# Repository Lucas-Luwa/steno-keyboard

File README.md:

# Stenography keyboard

A custom 30-key stenography keyboard with a Waveshare RP2040-Plus 16 MB controller, Kailh Choc V1 switches, eight RGB LEDs, and a 3D-printed case with a removable travel cap.

**[V3](V3/) is the latest version.** Earlier electronics designs and case exports are in [archive/](archive/README.md).

## Start here

| What you need | Open |
|---|---|
| Assembly instructions | [Build guide](V3/build-guide.md) |
| Schematic, PCB and parts | [Electronics](V3/hardware/README.md) · [KiCad project](V3/hardware/StenoV3.kicad_pro) · [BOM](V3/hardware/bom.csv) |
| Editable CAD, STL models and printer jobs | [Mechanical guide](V3/mechanical/README.md) |
| Gerbers and drill files | [Fabrication guide](V3/manufacturing/README.md) · [Fabrication ZIP](V3/manufacturing/StenoV3-Gerbers.zip) |
| Javelin configuration and LED diagnostics | [Firmware guide](V3/firmware/README.md) |
| LED diagnostics and test results | [LED test guide](V3/firmware/led-tests/README.md) · [Results](V3/firmware/led-tests/results.md) |
| Switch-library credits and licenses | [Reference assets](third_party/README.md) |

## Onboard lighting

The keyboard uses [Javelin firmware with Lapwing dictionaries](V3/firmware/javelin/README.md) for onboard stenography. The lighting runs on the controller, with selectable idle patterns, brightness controls and a green typing indicator.

https://github.com/user-attachments/assets/ecf25d7d-600b-45e7-80ae-683e2c61e2ce

Onboard lighting patterns and controls.

## Design files

The [mechanical guide](V3/mechanical/README.md) covers the base, travel cap, insert coupon, LED jig references and keyboard assemblies.

For printing, start with [`case-bottom.stl`](V3/mechanical/stl/case-bottom.stl), [`travel-cap.stl`](V3/mechanical/stl/travel-cap.stl) and [`insert-test-coupon.stl`](V3/mechanical/stl/insert-test-coupon.stl). The [SV06/OrcaSlicer profile](V3/mechanical/README.md#sv06-slicing-settings) covers PLA settings and diagonal bed placement. Slice the current travel cap from its STL. Bambu-specific base and insert-coupon printer jobs for A1, P1S and P2S are grouped under [`print-jobs/`](V3/mechanical/print-jobs/).

The [electronics guide](V3/hardware/README.md) explains component packages, the five-row/six-column matrix and the RGB chain. GPIO assignments, switch/diode positions and LED order are also available as CSV tables alongside the KiCad project.

## Repository layout

```text
steno/
├── README.md
├── V3/
│   ├── build-guide.md
│   ├── hardware/        # KiCad project, BOM, pinout and matrix
│   ├── mechanical/
│   │   ├── solidworks/ # Editable parts and assemblies
│   │   ├── step/       # Neutral CAD references
│   │   ├── stl/        # Case, coupon and LED jig reference meshes
│   │   └── print-jobs/ # A1, P1S and P2S base/coupon jobs
│   ├── manufacturing/ # Fabrication ZIP and individual Gerbers/drills
│   ├── firmware/       # Javelin hardware configuration and LED diagnostics
│   └── images/         # Build photos, diagrams and videos
├── archive/            # Earlier electronics versions and case exports
└── third_party/        # Reference-asset credits and license texts
```

## Credits

[Javelin](https://github.com/jthlim/javelin-steno-pico) by its contributors. Kailh Choc switch footprint and models from [keyswitch-kicad-library](https://github.com/perigoso/keyswitch-kicad-library). See [third_party/](third_party/README.md) for the bundled notices.

## License

See [LICENSE.md](LICENSE.md) for hardware, software, documentation and third-party license terms.

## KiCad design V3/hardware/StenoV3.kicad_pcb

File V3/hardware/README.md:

# Electronics

Open [`StenoV3.kicad_pro`](StenoV3.kicad_pro) in KiCad 10 with the standard symbol, footprint and 3D libraries installed.

Bare PCB before component installation. Follow the [illustrated build guide](../build-guide.md#3-assemble-the-electronics) for the populated board and switch stages.

## Circuit specifications

| Item | Specification |
|---|---|
| Controller | Waveshare RP2040-Plus-16MB |
| Switch matrix | 30 positions, 5 rows × 6 columns |
| Switches | Kailh Choc V1 |
| Row pins | GP0–GP4, connected to diode cathodes |
| Column pins | GP5–GP10, connected to switch sides |
| LED data | GP22 → U1 → R3 (330 Ω) → LEDs |
| RGB LEDs | Eight 5 × 5 mm WS2812B LEDs in a serial chain |
| Bypass capacitors | Nine × 100 nF, 0805 |
| Mounting holes | Eight × 2.2 mm for M2 screws |
| PCB | Two copper layers, 1.6 mm thickness; approximately 252 × 68 mm |

A1 uses the generic `RaspberryPi_Pico` symbol, footprint and 3D model. Fit the Waveshare module with its USB-C connector aligned to the case opening.

## Parts and connections

- [Bill of materials](bom.csv): component quantities, references, schematic values, footprints and package notes.
- [Controller pinout](pinout.csv): GPIO functions and physical module pad numbers.
- [Electrical key matrix](key-matrix.csv): each switch, its diode and its PCB position.
- [LED chain](led-chain.csv): zero-based LED order, beginning at R3.

Use the matrix's row/column coordinates when assigning firmware key actions. Electrical matrix positions are independent of physical keyboard rows.

## Parts sourcing

The parts for this build came from these suppliers:

| Item | Source |
|---|---|
| Electronic components and assembly hardware | AliExpress |
| Custom PCB fabrication | AIVON |
| Waveshare RP2040-Plus-16MB controller | RobotShop |

PCB ordering files are in the [fabrication guide](../manufacturing/README.md).

## Component packages

| Reference | Part / package | Schematic label |
|---|---|---|
| A1 | Waveshare RP2040-Plus-16MB, castellated Pico-compatible module | `RaspberryPi_Pico` |
| D2–D45, populated positions listed in BOM | 1N4148-family switching diode, **SOD-323**; e.g. 1N4148WS | `1N4148W` |
| LED8–LED28, populated positions listed in BOM | WS2812B, **5 × 5 mm four-pin** | `WS2812C` |
| U1 | Single buffer, **SOT-23-5**; see buffer options below | `74AHCT1G125` |
| F1 | MF_MSMF050-2 resettable fuse, **1812** | `MF_MSMF050-2` |

Diode package and cathode marking: [1N4148WS datasheet](https://www.diodes.com/datasheet/download/1N4148WS.pdf).

## LED buffer

The PCB's U1 connections are:

| Pin | PCB connection |
|---|---|
| 1 | Ground |
| 2 | GP22 input |
| 3 | Ground |
| 4 | R3 → first LED DIN |
| 5 | Fused USB 5 V |

The SOT-23-5 options are **74AHCT1G125** and **SN74LV1T34DBVR**. Pin 1 grounds the AHCT buffer's active-low enable; the LV1T34 leaves pin 1 internally unconnected. Both use pins 2–5 for input, ground, output and supply. Use the DBV/SOT-23-5 package. See the [74AHCT1G125](https://www.ti.com/lit/ds/symlink/sn74ahct1g125.pdf) and [SN74LV1T34](https://www.ti.com/lit/ds/symlink/sn74lv1t34.pdf) pin tables.

## Matrix and RGB configuration

Scan GP0–GP4 as cathode rows, selecting one row low at a time and reading GP5–GP10 with pull-ups. Leave unselected rows inactive.

The RGB chain is **LED17 → LED16 → LED15 → LED14 → LED13 → LED12 → LED8 → LED28**. The [lighting configuration](../firmware/javelin/README.md#onboard-lighting) includes the firmware's estimated LED-current limit.

## Board views

Use the [front layout](../images/pcb-front.svg), [back layout](../images/pcb-back.svg) and [schematic](../images/schematic.svg) to identify pads and component orientations.

## Libraries and models

The custom Choc footprint is under `libraries/`; the footprint table uses a project-relative path. Switch and fuse models are under `models/`. Standard models use `${KICAD10_3DMODEL_DIR}`.

Continue with the [build guide](../build-guide.md) or [firmware configuration](../firmware/README.md).

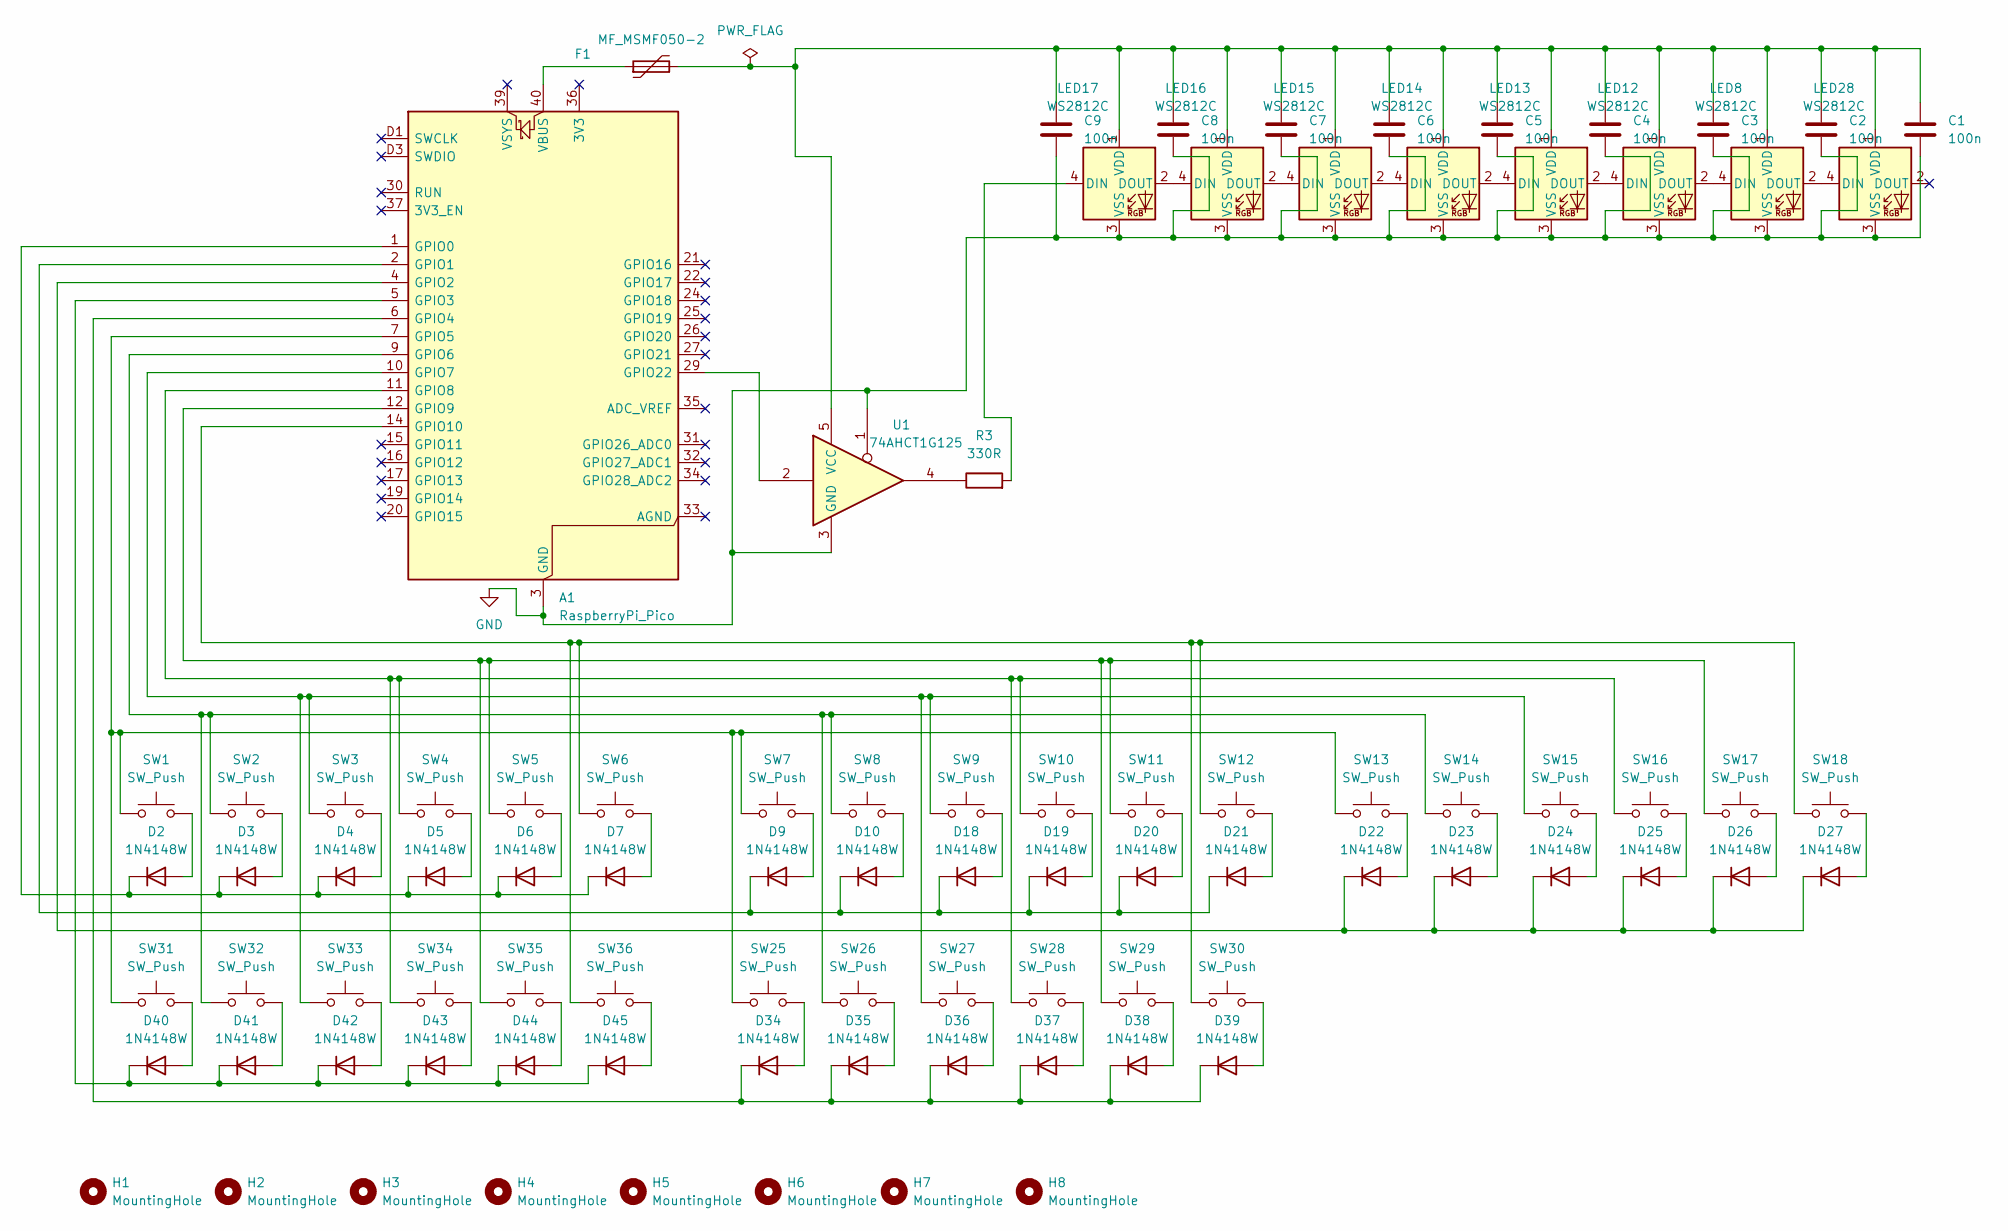
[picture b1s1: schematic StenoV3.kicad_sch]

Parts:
A1: RaspberryPi_Pico; RaspberryPi_Pico_SMD_HandSolder
C1, C2, C3, C4, C5, C6, C7, C8, C9: 100n; C_0805_2012Metric_Pad1.18x1.45mm_HandSolder
D2, D3, D4, D5, D6, D7, D9, D10, D18, D19, D20, D21, D22, D23, D24, D25, D26, D27, D34, D35, D36, D37, D38, D39, D40, D41, D42, D43, D44, D45: 1N4148W; D_SOD-323_HandSoldering
F1: MF_MSMF050-2; Fuse_1812_4532Metric_Pad1.30x3.40mm_HandSolder
H1, H2, H3, H4, H5, H6, H7, H8: MountingHole; MountingHole_2.2mm_M2
LED8, LED12, LED13, LED14, LED15, LED16, LED17, LED28: WS2812C; LED_WS2812B_PLCC4_5.0x5.0mm_P3.2mm
R3: 330R; R_0805_2012Metric_Pad1.20x1.40mm_HandSolder
SW1, SW2, SW3, SW4, SW5, SW6, SW7, SW8, SW9, SW10, SW11, SW12, SW13, SW14, SW15, SW16, SW17, SW18, SW25, SW26, SW27, SW28, SW29, SW30, SW31, SW32, SW33, SW34, SW35, SW36: SW_Push; SW_Kailh_Choc_V1_1.00u
U1: 74AHCT1G125; SOT-23-5_HandSoldering

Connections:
GND: A1.3 (GND), A1.8 (GND), A1.13 (GND), A1.18 (GND), A1.23 (GND), A1.28 (GND), A1.38 (GND), A1.D2 (GND), C1.2, C2.2, C3.2, C4.2, C5.2, C6.2, C7.2, C8.2, C9.2, LED8.3 (VSS), LED12.3 (VSS), LED13.3 (VSS), LED14.3 (VSS), LED15.3 (VSS), LED16.3 (VSS), LED17.3 (VSS), LED28.3 (VSS), U1.1, U1.3 (GND)
unnamed: A1.1 (GPIO0), D2.1 (K), D3.1 (K), D4.1 (K), D5.1 (K), D6.1 (K), D7.1 (K)
unnamed: A1.2 (GPIO1), D9.1 (K), D10.1 (K), D18.1 (K), D19.1 (K), D20.1 (K), D21.1 (K)
unnamed: A1.4 (GPIO2), D22.1 (K), D23.1 (K), D24.1 (K), D25.1 (K), D26.1 (K), D27.1 (K)
unnamed: A1.5 (GPIO3), D40.1 (K), D41.1 (K), D42.1 (K), D43.1 (K), D44.1 (K), D45.1 (K)
unnamed: A1.6 (GPIO4), D34.1 (K), D35.1 (K), D36.1 (K), D37.1 (K), D38.1 (K), D39.1 (K)
unnamed: A1.7 (GPIO5), SW1.1, SW7.1, SW13.1, SW25.1, SW31.1
unnamed: A1.9 (GPIO6), SW2.1, SW8.1, SW14.1, SW26.1, SW32.1
unnamed: A1.10 (GPIO7), SW3.1, SW9.1, SW15.1, SW27.1, SW33.1
unnamed: A1.11 (GPIO8), SW4.1, SW10.1, SW16.1, SW28.1, SW34.1
unnamed: A1.12 (GPIO9), SW5.1, SW11.1, SW17.1, SW29.1, SW35.1
unnamed: A1.14 (GPIO10), SW6.1, SW12.1, SW18.1, SW30.1, SW36.1
unnamed: A1.29 (GPIO22), U1.2
unnamed: A1.40 (VBUS), F1.1
unnamed: D2.2 (A), SW1.2
unnamed: D3.2 (A), SW2.2
unnamed: D4.2 (A), SW3.2
unnamed: D5.2 (A), SW4.2
unnamed: D6.2 (A), SW5.2
unnamed: D7.2 (A), SW6.2
unnamed: D9.2 (A), SW7.2
unnamed: D10.2 (A), SW8.2
unnamed: D18.2 (A), SW9.2
unnamed: D19.2 (A), SW10.2
unnamed: D20.2 (A), SW11.2
unnamed: D21.2 (A), SW12.2
unnamed: D22.2 (A), SW13.2
unnamed: D23.2 (A), SW14.2
unnamed: D24.2 (A), SW15.2
unnamed: D25.2 (A), SW16.2
unnamed: D26.2 (A), SW17.2
unnamed: D27.2 (A), SW18.2
unnamed: D34.2 (A), SW25.2
unnamed: D35.2 (A), SW26.2
unnamed: D36.2 (A), SW27.2
unnamed: D37.2 (A), SW28.2
unnamed: D38.2 (A), SW29.2
unnamed: D39.2 (A), SW30.2
unnamed: D40.2 (A), SW31.2
unnamed: D41.2 (A), SW32.2
unnamed: D42.2 (A), SW33.2
unnamed: D43.2 (A), SW34.2
unnamed: D44.2 (A), SW35.2
unnamed: D45.2 (A), SW36.2
unnamed: LED12.4 (DIN), LED13.2 (DOUT)
unnamed: LED8.4 (DIN), LED12.2 (DOUT)
unnamed: C1.1, C2.1, C3.1, C4.1, C5.1, C6.1, C7.1, C8.1, C9.1, F1.2, LED8.1 (VDD), LED12.1 (VDD), LED13.1 (VDD), LED14.1 (VDD), LED15.1 (VDD), LED16.1 (VDD), LED17.1 (VDD), LED28.1 (VDD), U1.5 (VCC)
unnamed: LED13.4 (DIN), LED14.2 (DOUT)
unnamed: LED14.4 (DIN), LED15.2 (DOUT)
unnamed: LED15.4 (DIN), LED16.2 (DOUT)
unnamed: LED16.4 (DIN), LED17.2 (DOUT)
unnamed: LED17.4 (DIN), R3.2
unnamed: LED8.2 (DOUT), LED28.4 (DIN)
unnamed: R3.1, U1.4

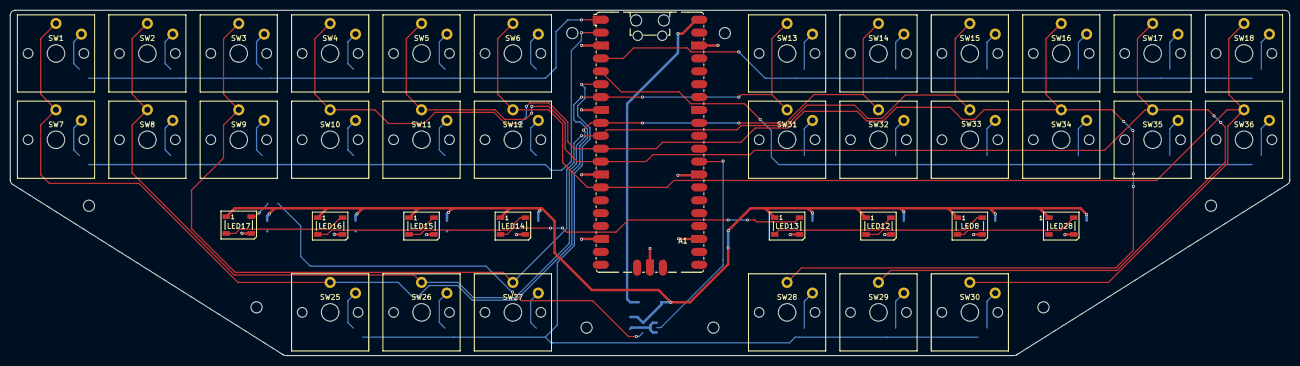
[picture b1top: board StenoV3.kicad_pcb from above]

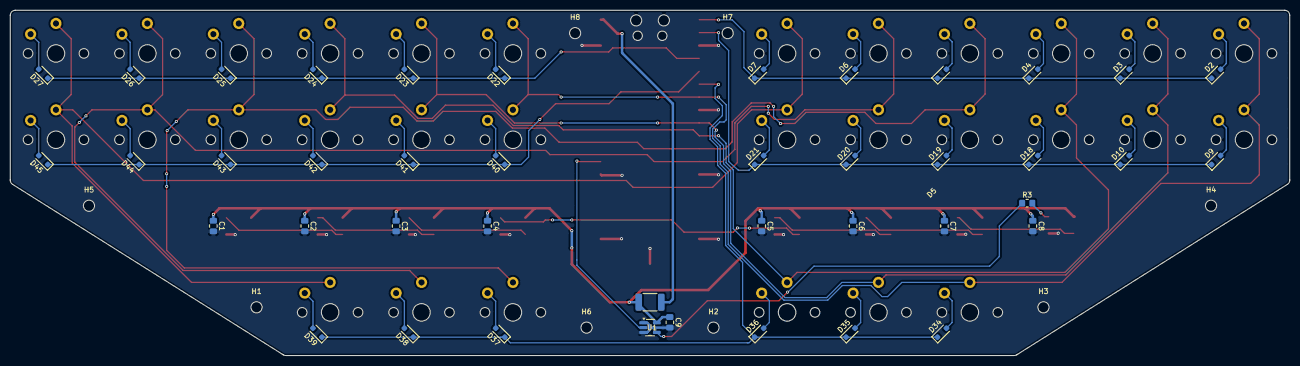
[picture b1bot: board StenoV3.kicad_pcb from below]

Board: 2 copper layers, 252.0 x 68.0 mm, 89 parts (42 on the bottom side), 54 nets.

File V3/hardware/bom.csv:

quantity,references,value,footprint,notes
9,C1 C2 C3 C4 C5 C6 C7 C8 C9,100n,Capacitor_SMD:C_0805_2012Metric_Pad1.18x1.45mm_HandSolder,100 nF capacitor; 0805.
30,D2 D3 D4 D5 D6 D7 D9 D10 D18 D19 D20 D21 D22 D23 D24 D25 D26 D27 D34 D35 D36 D37 D38 D39 D40 D41 D42 D43 D44 D45,1N4148W,Diode_SMD:D_SOD-323_HandSoldering,1N4148-family diode in SOD-323 (e.g. 1N4148WS); band marks cathode.
1,R3,330R,Resistor_SMD:R_0805_2012Metric_Pad1.20x1.40mm_HandSolder,330 ohm LED data resistor; 0805.
1,U1,74AHCT1G125,Package_TO_SOT_SMD:SOT-23-5_HandSoldering,SOT-23-5 buffer; 74AHCT1G125 or SN74LV1T34DBVR. Pin connections: hardware guide.
1,F1,MF_MSMF050-2,Fuse:Fuse_1812_4532Metric_Pad1.30x3.40mm_HandSolder,Resettable fuse; 1812.
8,H1 H2 H3 H4 H5 H6 H7 H8,MountingHole,MountingHole:MountingHole_2.2mm_M2,2.2 mm PCB clearance hole for M2 screw.
1,A1,RaspberryPi_Pico,Module:RaspberryPi_Pico_SMD_HandSolder,Waveshare RP2040-Plus-16MB; Pico-compatible castellated footprint.
30,SW1 SW2 SW3 SW4 SW5 SW6 SW7 SW8 SW9 SW10 SW11 SW12 SW13 SW14 SW15 SW16 SW17 SW18 SW25 SW26 SW27 SW28 SW29 SW30 SW31 SW32 SW33 SW34 SW35 SW36,SW_Push,Switch_Keyboard_Kailh:SW_Kailh_Choc_V1_1.00u,Kailh Choc V1 switch.
8,LED8 LED12 LED13 LED14 LED15 LED16 LED17 LED28,WS2812C,LED_SMD:LED_WS2812B_PLCC4_5.0x5.0mm_P3.2mm,WS2812B RGB LED; 5 x 5 mm four-pin footprint. WS2812C is the schematic value label.
